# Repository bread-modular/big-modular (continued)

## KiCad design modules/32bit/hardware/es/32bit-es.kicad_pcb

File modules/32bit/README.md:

# 32bit — ESP32-S3 + CS4272 stereo audio processor (6HP)

S4 (2026-11-23): two boards. The **carrier** is the modules/usb-audio S5 analog board (CS4272 codec with
its own 24.576 MHz clock, NE5532 input / output stages, AMS1117 +5VA, DC-coupled ±5 V, 2 in / 2 out) with
two control pots, a MODE button and an LED in place of the volume pots. The **MCU board** (ESP32-S3R8,
8 MB PSRAM inside, W25Q128JVSIQ 16 MB flash, 40 MHz crystal) is soldered on two 1x10 strips over the
carrier's front side and carries the USB-C, which comes out through the front panel. Two M3x10 standoffs
above the MCU board take the plug forces. It runs the `master` end-of-chain processor in front of PA
systems; the reason for the codec change is in `docs/research.md` section 9. The S3 design (one board,
ES8388, MIDI and CV inputs, USB-C on the back) is in git history.

**ES1 variant (2026-11-23, `hardware/es/`, `docs/research.md` section 10):** the S3 board (ES8388, MIDI in,
2 audio + 2 CV in, back USB-C) with its own codec supply (LP5907 from +5V) and its own codec clock (11.2896 MHz
oscillator, ES8388 = I2S master), to build next to S4 and compare. Firmware: `BOARD=es1 ./compile.sh ...`.
Hand-routed, ERC 0 / DRC 0, JLCPCB export in [`jlcpcb/es/`](jlcpcb/es/README.md); not built.

| Panel (top to bottom) | Circuit |
|---|---|
| **USB** (USB-C) | MCU board J101 -> USBLC6-2SC6 -> ESP32-S3 GPIO19 / 20 (USB Serial/JTAG: Web Serial, console, firmware download). Data only, VBUS powers nothing |
| **IN L**, **IN R** | jack -> 1k -> NE5532 follower -> OPA1679 differential drive on +5VA -> CS4272 ADC (±5.5 V full scale, 100k input) |
| **P1**, **P2** | 50k RV09 from a filtered 3.03 V -> ESP32-S3 ADC1 (GPIO7 / GPIO6). Firmware controls, not in the audio path |
| LED, **MODE** | 3 mm red LED on GPIO39 (1k), 6 x 6 mm tact switch on GPIO38 (to GND) |
| **OUT L**, **OUT R** | CS4272 DAC (differential) -> NE5532 difference amplifier (±12 V) -> 1k -> jack (±5.3 V full scale) |

The ESP32-S3 is the I2S slave of the codec (SCLK GPIO18, LRCK GPIO17, data GPIO16 / GPIO13) and sets it
up over I2C (0x10, GPIO9 / GPIO8). Full pin map: [`docs/firmware-pins.md`](docs/firmware-pins.md).

Power: Eurorack 10-pin, ±12 V through series Schottkys; +12 V -> AMS1117-5.0 -> +5VA (codec analog side);
+12 V -> 22R 1 W -> AMS1117-3.3 -> +3V3 (MCU board, codec digital side behind a ferrite). About 130 mA
on +3V3 (datasheet estimate), so roughly 0.2 A from +12 V and 20 mA from -12 V; not measured. RESET and
BOOT buttons are on the carrier's back.

**Status: carrier S4 / R2 + MCU board S1 / R2, both hand-routed, 4 layers; panel P2. ERC 0, DRC 0,
0 unconnected, parity 0 on both boards. JLCPCB export in [`jlcpcb/`](jlcpcb/README.md) (two orders:
carrier 88 parts bottom side + panel, MCU board 25 parts top side, Economic PCBA). Fab-reviewed
2026-11-23; not supplier-accepted, not built.** The `master` firmware still needs its CS4272 driver.

| Path | Contents |
|---|---|
| `hardware/` | `32bit.kicad_{pro,sch,pcb}` (29 x 110 mm carrier) and `32bit-mcu.kicad_{pro,sch,pcb}` (29 x 29.55 mm MCU board), pinned symbols / footprints (`32BIT.kicad_sym`, `32BIT.pretty` + `PROVENANCE.json`, `32BIT.3dshapes`) |
| `panels/front-pcb/32bit-panel.kicad_{pro,pcb}` | 6HP FR4 front panel: NPTH only, USB-C slot, silkscreen labels |
| `panels/front-cad/` | FreeCAD printable panel (`.FCStd`, `.step`, `.stl`) generated from the panel PCB |
| `docs/research.md` | Decisions and circuit notes; section 9 is S4, 9.2 the fab review |
| `docs/geometry.json` | 6HP panel, placement and stack contract |
| `docs/32bit-schematic.pdf`, `docs/32bit-mcu-schematic.pdf`, `docs/fit/` | Schematic PDFs; native ERC / DRC JSON; assembly renders |
| `jlcpcb/` | JLCPCB Gerbers, BOM, CPL, upload map and sourcing notes |
| `firmware/` | `master`, `fxrack`, `polysynth` (ESP-IDF); see `firmware/README.md` |
| `tools/` | Generators (`circuit_carrier.py`, `circuit_mcu.py` hold the circuit tables), checks and the shared-tool profiles |

Checks (from `modules/32bit`):

```sh
python3 -B ../../opt/kicad-tools/kicad_tools.py check --config tools/kicad-project.json --reports research/check-NEW
python3 -B ../../opt/kicad-tools/kicad_tools.py check --config tools/kicad-project-mcu.json --reports research/check-mcu-NEW
python3 -B tools/check_edges.py     # courtyards to the edge, SMD to pot / jack pads
python3 -B tools/render_fit.py      # docs/fit/ renders of the stack
```

Both boards are routed by hand: `tools/build_layout.py` only rebuilds the panel now (`build_layout.py panel`).
Read [`Code.md`](Code.md) before changing hardware.

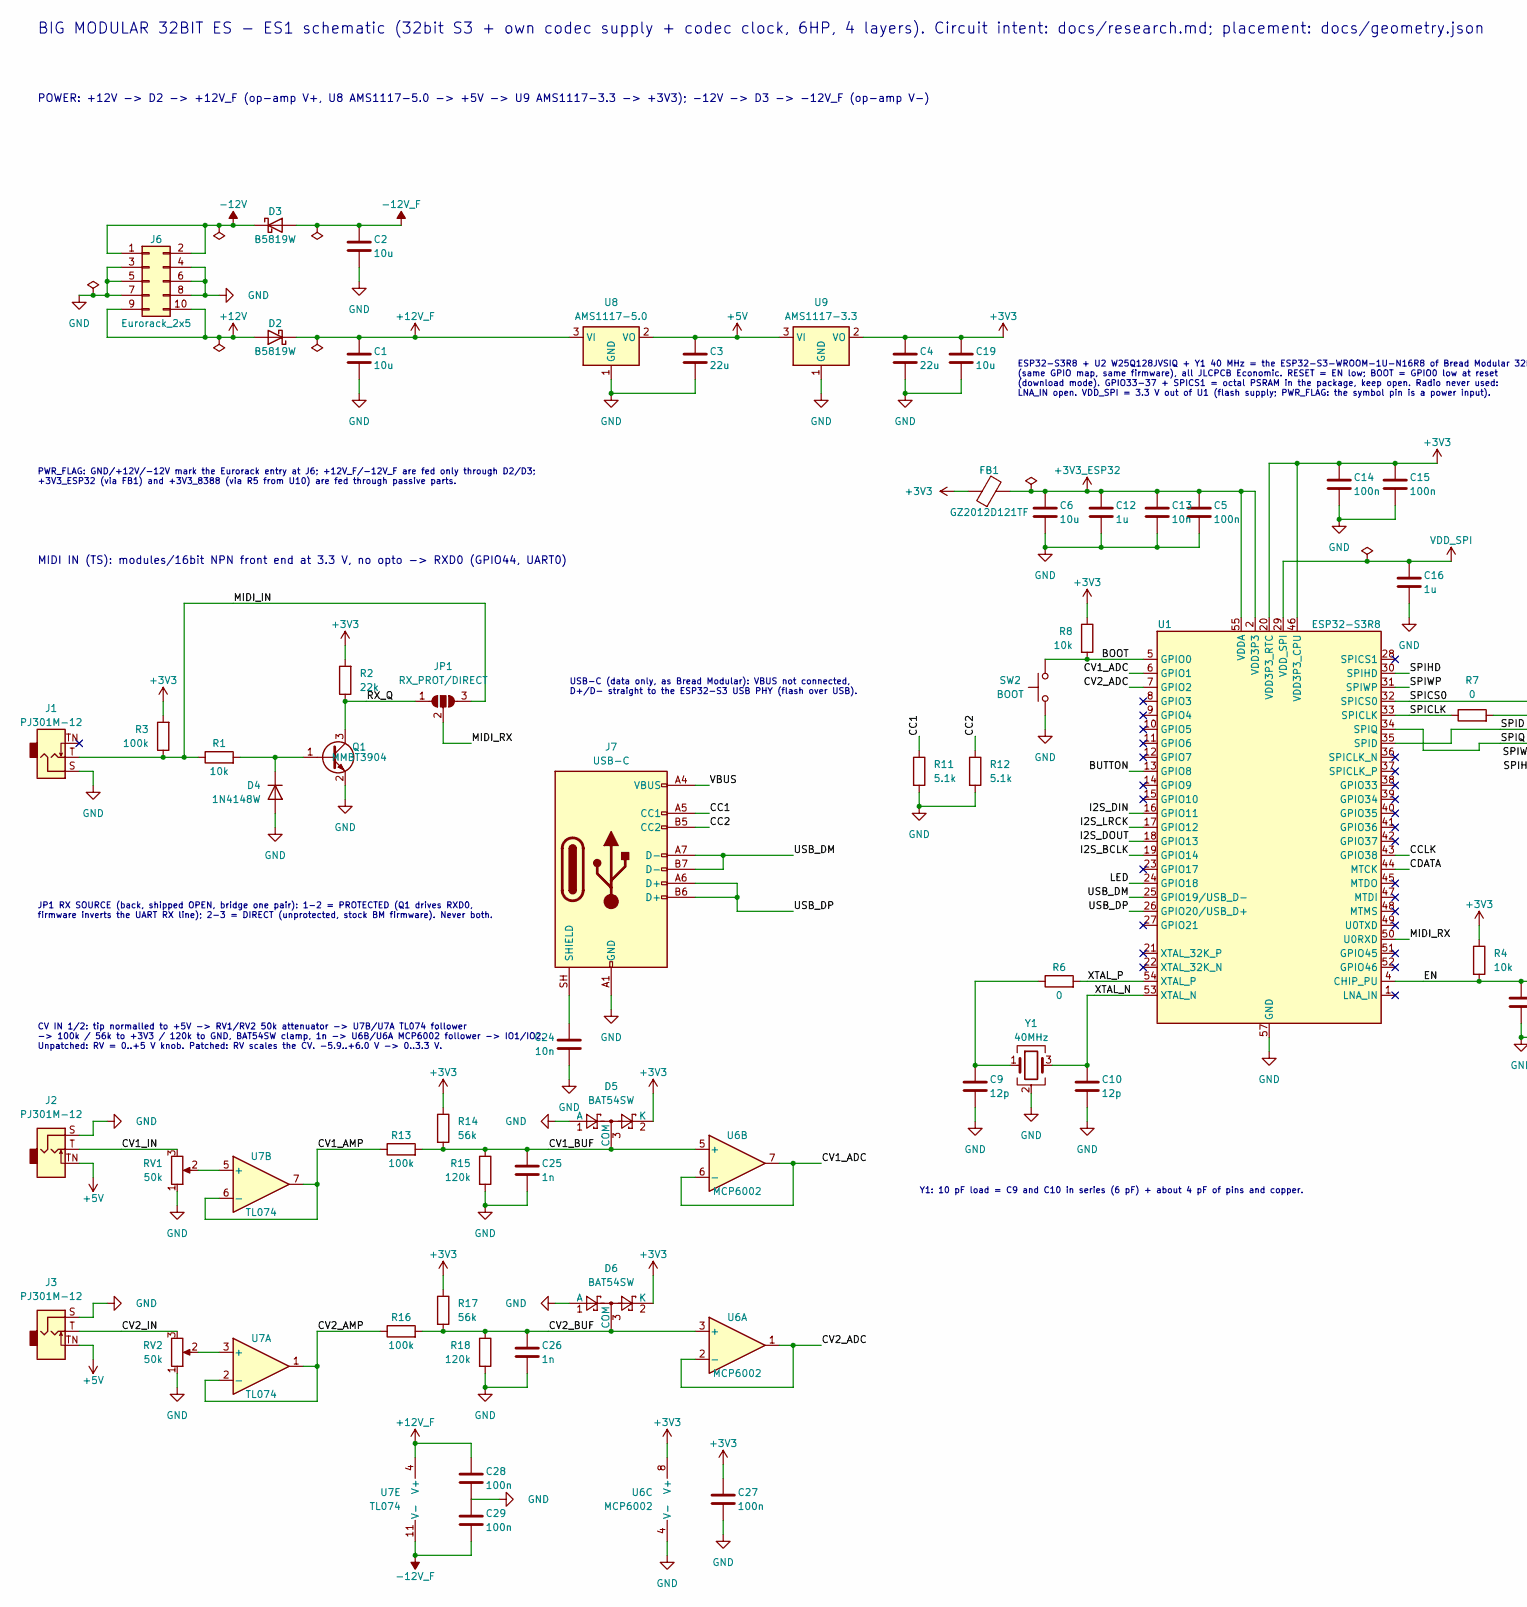
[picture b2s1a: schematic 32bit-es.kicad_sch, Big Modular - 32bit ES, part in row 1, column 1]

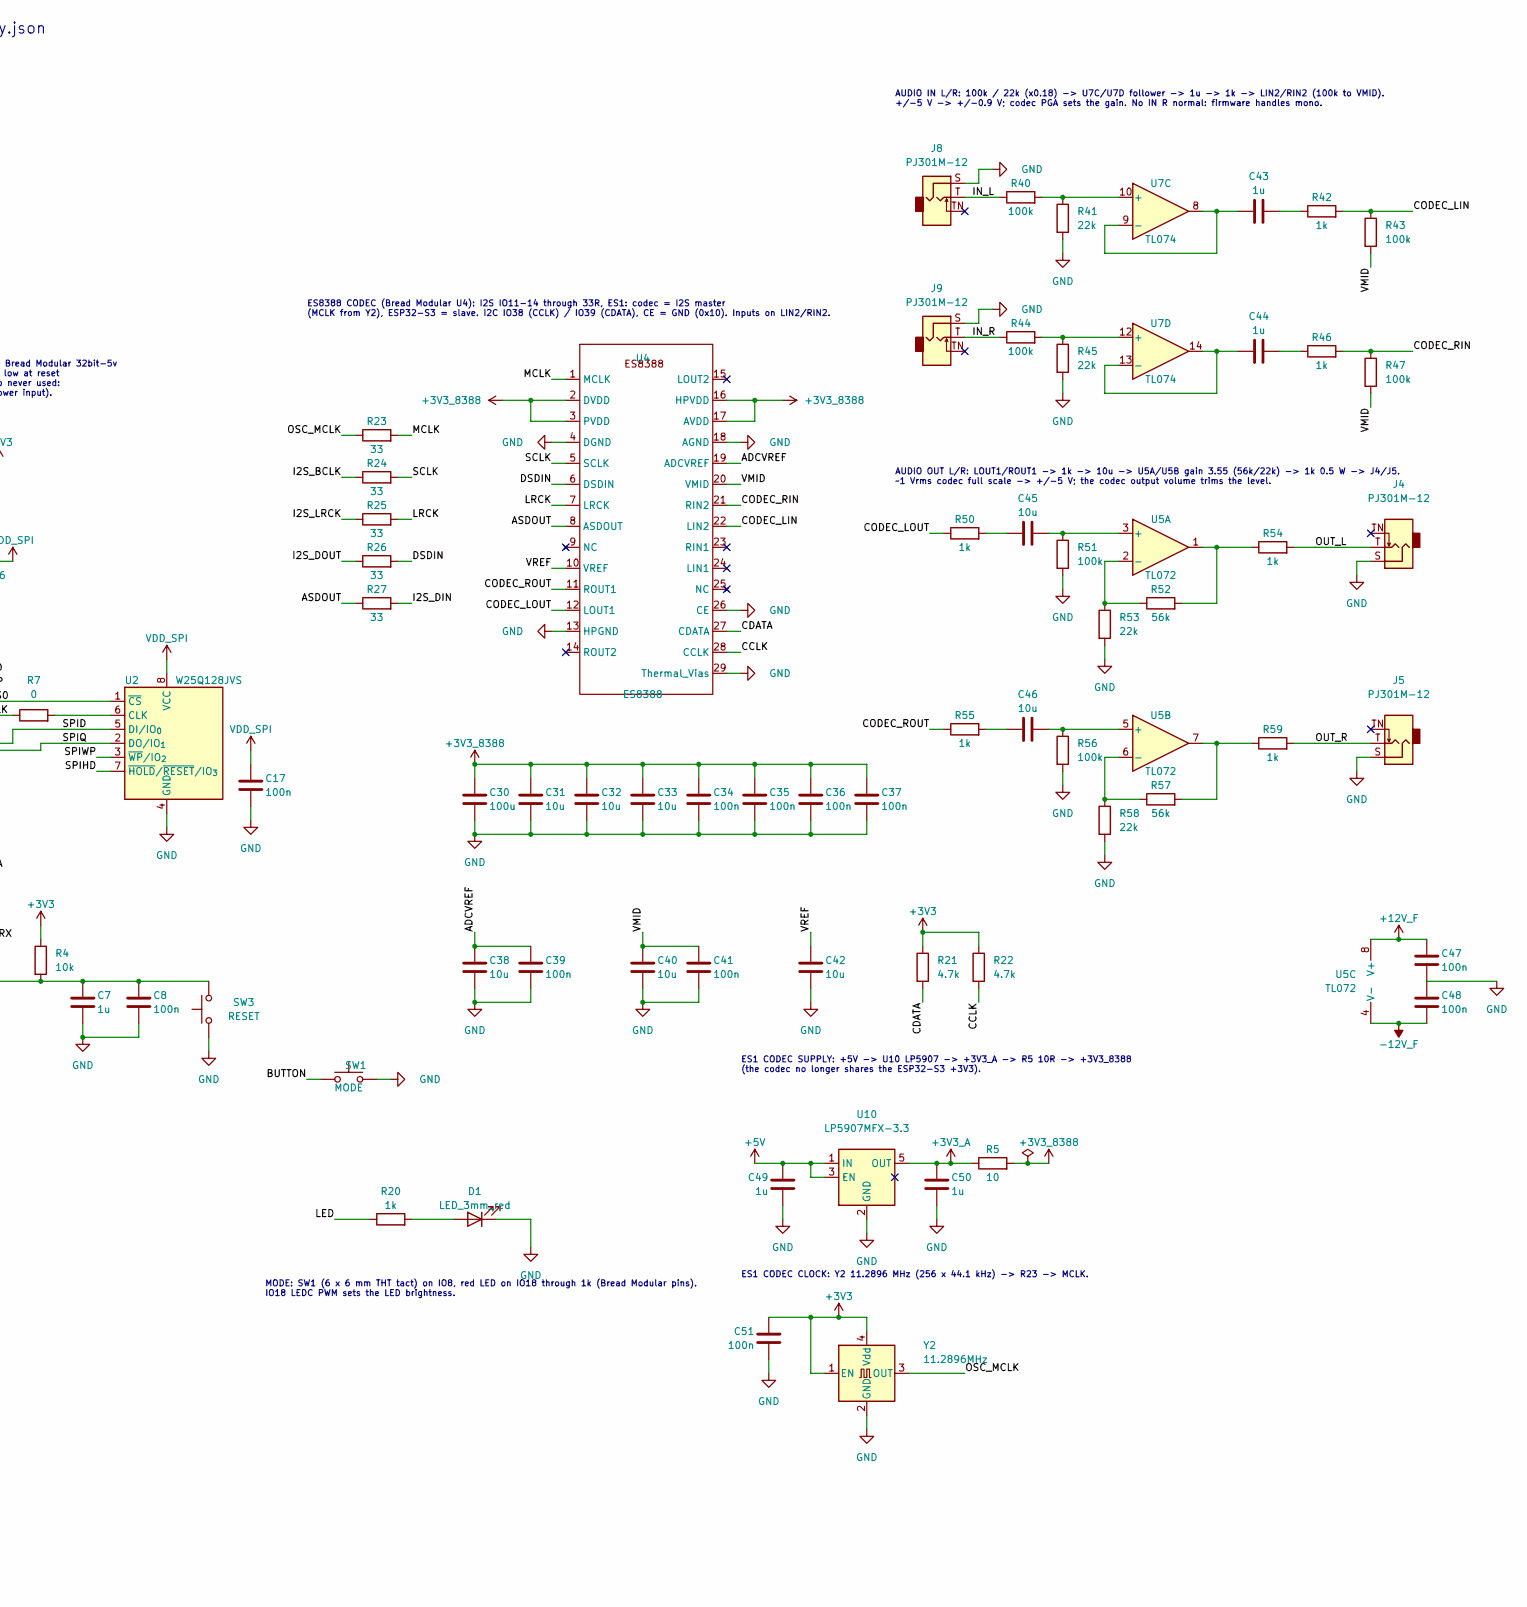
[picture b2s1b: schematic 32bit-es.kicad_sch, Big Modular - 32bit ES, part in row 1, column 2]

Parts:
C1, C2, C19, C45, C46: 10u; C_0805_2012Metric; Voltage 25V; MPN CL21A106KAYNNNE; LCSC C15850
C3, C4: 22u; C_0805_2012Metric; Voltage 25V; MPN CL21A226MAQNNNE; LCSC C45783
C5, C8, C14, C15, C17, C34, C35, C36, C37, C39, C41, C51: 100n; C_0402_1005Metric; Voltage 16V; MPN CL05B104KO5NNNC; LCSC C1525
C6: 10u; C_0603_1608Metric; Voltage 10V; MPN CL10A106KP8NNNC; LCSC C19702
C7, C12, C16, C43, C44, C49, C50: 1u; C_0402_1005Metric; Voltage 25V; MPN CL05A105KA5NQNC; LCSC C52923
C9, C10: 12p; C_0402_1005Metric; Voltage 50V; MPN 0402CG120J500NT; LCSC C1547
C13, C24: 10n; C_0402_1005Metric; Voltage 50V; MPN CL05B103KB5NNNC; LCSC C15195
C25, C26: 1n; C_0603_1608Metric; Voltage 50V; MPN CL10B102KB8NNNC; LCSC C1588
C27, C28, C29, C47, C48: 100n; C_0603_1608Metric; Voltage 50V; MPN CC0603KRX7R9BB104; LCSC C14663
C30: 100u; C_1206_3216Metric; Voltage 6.3V; MPN CL31A107MQHNNNE; LCSC C15008
C31, C32, C33, C38, C40, C42: 10u; C_0402_1005Metric; Voltage 10V; MPN CL05A106MQ5NUNC; LCSC C15525
D1: LED_3mm_red; LED_D3.0mm
D2, D3: B5819W; D_SOD-123; MPN B5819W SL; LCSC C8598
D4: 1N4148W; D_SOD-123; MPN 1N4148W; LCSC C81598
D5, D6: BAT54SW; SOT-323_SC-70; MPN BAT54SWT1G; LCSC C78260
FB1: GZ2012D121TF; C_0805_2012Metric; MPN GZ2012D121TF; LCSC C5671
J1, J2, J3, J4, J5, J8, J9: PJ301M-12; Jack_3.5mm_QingPu_WQP-PJ301M-12_Vertical
J6: Eurorack_2x5; PinHeader_2x05_P2.54mm_Vertical
J7: USB-C; USB_C_Receptacle_HRO_TYPE-C-31-M-12; MPN TYPE-C-31-M-12; LCSC C165948
JP1: RX_PROT/DIRECT; SolderJumper-3_P1.3mm_Open_RoundedPad1.0x1.5mm
Q1: MMBT3904; SOT-23; MPN MMBT3904(RANGE:100-300); LCSC C20526
R1: 10k; R_0603_1608Metric; MPN 0603WAF1002T5E; LCSC C25804
R2, R41, R45, R53, R58: 22k; R_0603_1608Metric; MPN 0603WAF2202T5E; LCSC C31850
R3, R13, R16, R40, R44, R51, R56: 100k; R_0603_1608Metric; MPN 0603WAF1003T5E; LCSC C25803
R4, R8: 10k; R_0402_1005Metric; MPN 0402WGF1002TCE; LCSC C25744
R5: 10; R_0603_1608Metric; MPN 0603WAF100JT5E; LCSC C22859
R6: 0; R_0402_1005Metric; MPN 0402WGF0000TCE; LCSC C17168
R7: 0; R_0603_1608Metric; MPN 0603WAF0000T5E; LCSC C21189
R11, R12: 5.1k; R_0402_1005Metric; MPN 0402WGF5101TCE; LCSC C25905
R14, R17, R52, R57: 56k; R_0603_1608Metric; MPN 0603WAF5602T5E; LCSC C23206
R15, R18: 120k; R_0603_1608Metric; MPN 0603WAF1203T5E; LCSC C25808
R20, R42, R46, R50, R55: 1k; R_0603_1608Metric; MPN 0603WAF1001T5E; LCSC C21190
R21, R22: 4.7k; R_0402_1005Metric; MPN 0402WGF4701TCE; LCSC C25900
R23, R24, R25, R26, R27: 33; R_0402_1005Metric; MPN 0402WGF330JTCE; LCSC C25105
R43, R47: 100k; R_0402_1005Metric; MPN 0402WGF1003TCE; LCSC C25741
R54, R59: 1k; R_1206_3216Metric; MPN 1206W4F1001T5E; LCSC C4410
RV1, RV2: 50k; Potentiometer_RV09
SW1: MODE; SW_PUSH_6mm_H7.3mm; MPN 6x6x7 mm THT tact switch, 4 pins (gener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
SW2: BOOT; K2-1808SN-A4SW-01; MPN K2-1808SN-A4SW-01; LCSC C92589
SW3: RESET; K2-1808SN-A4SW-01; MPN K2-1808SN-A4SW-01; LCSC C92589
U1: ESP32-S3R8; QFN-56-1EP_7x7mm_P0.4mm_EP4x4mm_ThermalVias; MPN ESP32-S3R8; LCSC C2913194
U2: W25Q128JVS; SOIC-8_5.3x5.3mm_P1.27mm; MPN W25Q128JVSIQ; LCSC C97521
U4: ES8388; ES8388_QFN28_4x4_P0.45_EP2.6_ThermalVias; MPN ES8388; LCSC C365736
U5: TL072; SOIC-8_3.9x4.9mm_P1.27mm; MPN TL072CDT; LCSC C6961
U6: MCP6002; SOIC-8_3.9x4.9mm_P1.27mm; MPN MCP6002T-I/SN; LCSC C7377
U7: TL074; SOIC-14_3.9x8.7mm_P1.27mm; MPN TL074CDR; LCSC C12594
U8: AMS1117-5.0; SOT-223-3_TabPin2; MPN AMS1117-5.0; LCSC C6187
U9: AMS1117-3.3; SOT-223-3_TabPin2; MPN AMS1117-3.3; LCSC C6186
U10: LP5907MFX-3.3; SOT-23-5; MPN LP5907MFX-3.3/NOPB; LCSC C80670
Y1: 40MHz; Crystal_SMD_3225-4Pin_3.2x2.5mm; MPN X322540MMB4SI; LCSC C5210647
Y2: 11.2896MHz; Oscillator_SMD_Abracon_ASE-4Pin_3.2x2.5mm; MPN OT322511.2896MJBA4SL; LCSC C2831381

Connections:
+3V3: C4.1, C14.1, C15.1, C19.1, C27.1, C51.1, D5.2 (K), D6.2 (K), FB1.1, R2.2, R3.2, R4.1, R8.1, R14.1, R17.1, R21.1, R22.1, U1.20 (VDD3P3_RTC), U1.46 (VDD3P3_CPU), U6.8 (V+), U9.2 (VO), Y2.1 (EN), Y2.4 (Vdd)
+3V3_8388: C30.1, C31.1, C32.1, C33.1, C34.1, C35.1, C36.1, C37.1, R5.2, U4.2 (DVDD), U4.3 (PVDD), U4.16 (HPVDD), U4.17 (AVDD)
+3V3_A: C50.1, R5.1, U10.5 (OUT)
+3V3_ESP32: C5.1, C6.1, C12.1, C13.1, FB1.2, U1.2 (VDD3P3), U1.3 (VDD3P3), U1.55 (VDDA), U1.56 (VDDA)
+5V: C3.1, C49.1, J2.TN, J3.TN, U8.2 (VO), U9.3 (VI), U10.1 (IN), U10.3 (EN)
+12V: D2.2 (A), J6.9, J6.10
+12V_F: C1.1, C28.1, C47.1, D2.1 (K), U5.8 (V+), U7.4 (V+), U8.3 (VI)
-12V: D3.1 (K), J6.1, J6.2
-12V_F: C2.2, C29.2, C48.2, D3.2 (A), U5.4 (V-), U7.11 (V-)
/ADCVREF: C38.1, C39.1, U4.19 (ADCVREF)
/ASDOUT: R27.1, U4.8 (ASDOUT)
/BOOT: R8.2, SW2.2, U1.5 (GPIO0)
/BUTTON: SW1.1, U1.13 (GPIO8)
/CC1: J7.A5 (CC1), R11.1
/CC2: J7.B5 (CC2), R12.1
/CCLK: R22.2, U1.43 (GPIO38), U4.28 (CCLK)
/CDATA: R21.2, U1.44 (MTCK), U4.27 (CDATA)
/CODEC_LIN: R42.2, R43.1, U4.22 (LIN2)
/CODEC_LOUT: R50.1, U4.12 (LOUT1)
/CODEC_RIN: R46.2, R47.1, U4.21 (RIN2)
/CODEC_ROUT: R55.1, U4.11 (ROUT1)
/CV1_ADC: U1.6 (GPIO1), U6.6 (-), U6.7
/CV1_AMP: R13.1, U7.6 (-), U7.7
/CV1_BUF: C25.1, D5.3 (COM), R13.2, R14.2, R15.1, U6.5 (+)
/CV1_IN: J2.T, RV1.3
/CV2_ADC: U1.7 (GPIO2), U6.1, U6.2 (-)
/CV2_AMP: R16.1, U7.1, U7.2 (-)
/CV2_BUF: C26.1, D6.3 (COM), R16.2, R17.2, R18.1, U6.3 (+)
/CV2_IN: J3.T, RV2.3
/DSDIN: R26.2, U4.6 (DSDIN)
/EN: C7.1, C8.1, R4.2, SW3.2, U1.4 (CHIP_PU)
/I2S_BCLK: R24.1, U1.19 (GPIO14)
/I2S_DIN: R27.2, U1.16 (GPIO11)
/I2S_DOUT: R26.1, U1.18 (GPIO13)
/I2S_LRCK: R25.1, U1.17 (GPIO12)
/IN_L: J8.T, R40.1
/IN_R: J9.T, R44.1
/LED: R20.1, U1.24 (GPIO18)
/LRCK: R25.2, U4.7 (LRCK)
/MCLK: R23.2, U4.1 (MCLK)
/MIDI_IN: J1.T, JP1.3 (B), R1.1, R3.1
/MIDI_RX: JP1.2 (C), U1.50 (U0RXD)
/OSC_MCLK: R23.1, Y2.3 (OUT)
/OUT_L: J4.T, R54.2
/OUT_R: J5.T, R59.2
/RX_Q: JP1.1 (A), Q1.3 (C), R2.1
/SCLK: R24.2, U4.5 (SCLK)
/SPICLK: R7.1, U1.33 (SPICLK)
/SPICS0: U1.32 (SPICS0), U2.1 (~CS)
/SPID: U1.35 (SPID), U2.5 (DI/IO_{0})
/SPIHD: U1.30 (SPIHD), U2.7 (~HOLD/~RESET/IO_{3})
/SPIQ: U1.34 (SPIQ), U2.2 (DO/IO_{1})
/SPIWP: U1.31 (SPIWP), U2.3 (~WP/IO_{2})
/USB_DM: J7.A7 (D-), J7.B7 (D-), U1.25 (GPIO19/USB_D-)
/USB_DP: J7.A6 (D+), J7.B6 (D+), U1.26 (GPIO20/USB_D+)
/VBUS: J7.A4 (VBUS), J7.A9 (VBUS), J7.B4 (VBUS), J7.B9 (VBUS)
/VMID: C40.1, C41.1, R43.2, R47.2, U4.20 (VMID)
/VREF: C42.1, U4.10 (VREF)
/XTAL_N: C10.1, U1.53 (XTAL_N), Y1.3
/XTAL_P: R6.2, U1.54 (XTAL_P)
GND: C1.2, C2.1, C3.2, C4.2, C5.2, C6.2, C7.2, C8.2, C9.2, C10.2, C12.2, C13.2, C14.2, C15.2, C16.2, C17.2, C19.2, C24.2, C25.2, C26.2, C27.2, C28.2, C29.1, C30.2, C31.2, C32.2, C33.2, C34.2, C35.2, C36.2, C37.2, C38.2, C39.2, C40.2, C41.2, C42.2, C47.2, C48.1, C49.2, C50.2, C51.2, D1.1 (K), D4.2 (A), D5.1 (A), D6.1 (A), J1.S, J2.S, J3.S, J4.S, J5.S, J6.3, J6.4, J6.5, J6.6, J6.7, J6.8, J7.A1 (GND), J7.A12 (GND), J7.B1 (GND), J7.B12 (GND), J8.S, J9.S, Q1.2 (E), R11.2, R12.2, R15.2, R18.2, R41.2, R45.2, R51.2, R53.2, R56.2, R58.2, RV1.1, RV2.1, SW1.2, SW2.1, SW3.1, U1.57 (GND), U2.4 (GND), U4.4 (DGND), U4.13 (HPGND), U4.18 (AGND), U4.26 (CE), U4.29 (Thermal_Vias), U6.4 (V-), U8.1 (GND), U9.1 (GND), U10.2 (GND), Y1.2 (G), Y1.4 (G), Y2.2 (GND)
unnamed: C9.1, R6.1, Y1.1
unnamed: C43.2, R42.1
unnamed: C44.2, R46.1
unnamed: C45.1, R50.2
unnamed: C46.1, R55.2
unnamed: D1.2 (A), R20.2
unnamed: D4.1 (K), Q1.1 (B), R1.2
unnamed: C24.1, J7.SH (SHIELD)
unnamed: R52.2, R54.1, U5.1
unnamed: R57.2, R59.1, U5.7
unnamed: R7.2, U2.6 (CLK)
unnamed: C45.2, R51.1, U5.3 (+)
unnamed: R52.1, R53.1, U5.2 (-)
unnamed: C46.2, R56.1, U5.5 (+)
unnamed: R57.1, R58.1, U5.6 (-)
unnamed: RV2.2, U7.3 (+)
unnamed: RV1.2, U7.5 (+)
unnamed: R40.2, R41.1, U7.10 (+)
unnamed: C43.1, U7.8, U7.9 (-)
unnamed: R44.2, R45.1, U7.12 (+)
unnamed: C44.1, U7.13 (-), U7.14
VDD_SPI: C16.1, C17.1, U1.29 (VDD_SPI), U2.8 (VCC)

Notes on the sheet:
USB-C (data only, as Bread Modular): VBUS not connected, D+/D- straight to the ESP32-S3 USB PHY (flash over USB).
MIDI IN (TS): modules/16bit NPN front end at 3.3 V, no opto -> RXD0 (GPIO44, UART0)
ES8388 CODEC (Bread Modular U4): I2S IO11-14 through 33R, ES1: codec = I2S master (MCLK from Y2), ESP32-S3 = slave. I2C IO38 (CCLK) / IO39 (CDATA), CE = GND (0x10). Inputs on LIN2/RIN2.
POWER: +12V -> D2 -> +12V_F (op-amp V+, U8 AMS1117-5.0 -> +5V -> U9 AMS1117-3.3 -> +3V3); -12V -> D3 -> -12V_F (op-amp V-)
JP1 RX SOURCE (back, shipped OPEN, bridge one pair): 1-2 = PROTECTED (Q1 drives RXD0, firmware inverts the UART RX line); 2-3 = DIRECT (unprotected, stock BM firmware). Never both.
ES1 CODEC SUPPLY: +5V -> U10 LP5907 -> +3V3_A -> R5 10R -> +3V3_8388 (the codec no longer shares the ESP32-S3 +3V3).
ES1 CODEC CLOCK: Y2 11.2896 MHz (256 x 44.1 kHz) -> R23 -> MCLK.
BIG MODULAR 32BIT ES - ES1 schematic (32bit S3 + own codec supply + codec clock, 6HP, 4 layers). Circuit intent: docs/research.md; placement: docs/geometry.json
AUDIO IN L/R: 100k / 22k (x0.18) -> U7C/U7D follower -> 1u -> 1k -> LIN2/RIN2 (100k to VMID). +/-5 V -> +/-0.9 V; codec PGA sets the gain. No IN R normal: firmware handles mono.
ESP32-S3R8 + U2 W25Q128JVSIQ + Y1 40 MHz = the ESP32-S3-WROOM-1U-N16R8 of Bread Modular 32bit-5v (same GPIO map, same firmware), all JLCPCB Economic. RESET = EN low; BOOT = GPIO0 low at reset (download mode). GPIO33-37 + SPICS1 = octal PSRAM in the package, keep open. Radio never used: LNA_IN open.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
CV IN 1/2: tip normalled to +5V -> RV1/RV2 50k attenuator -> U7B/U7A TL074 follower -> 100k / 56k to +3V3 / 120k to GND, BAT54SW clamp, 1n -> U6B/U6A MCP6002 follower -> IO1/IO2. Unpatched: RV = 0..+5 V knob. Patched: RV scales the CV. -5.9..+6.0 V -> 0..3.3 V.
PWR_FLAG: GND/+12V/-12V mark the Eurorack entry at J6; +12V_F/-12V_F are fed only through D2/D3; +3V3_ESP32 (via FB1) and +3V3_8388 (via R5 from U10) are fed through passive parts.
MODE: SW1 (6 x 6 mm THT tact) on IO8, red LED on IO18 through 1k (Bread Modular pins). IO18 LEDC PWM sets the LED brightness.
AUDIO OUT L/R: LOUT1/ROUT1 -> 1k -> 10u -> U5A/U5B gain 3.55 (56k/22k) -> 1k 0.5 W -> J4/J5. ~1 Vrms codec full scale -> +/-5 V; the codec output volume trims the level.
Y1: 10 pF load = C9 and C10 in series (6 pF) + about 4 pF of pins and copper.

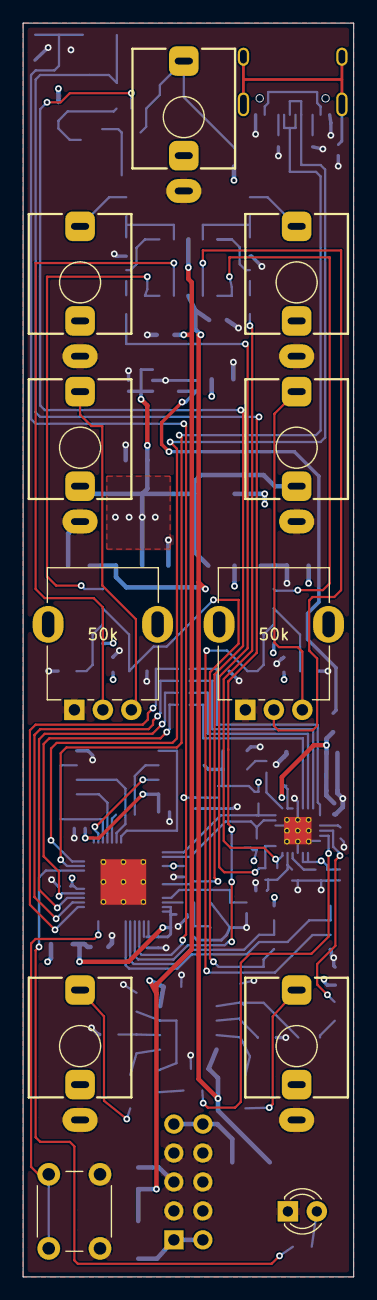
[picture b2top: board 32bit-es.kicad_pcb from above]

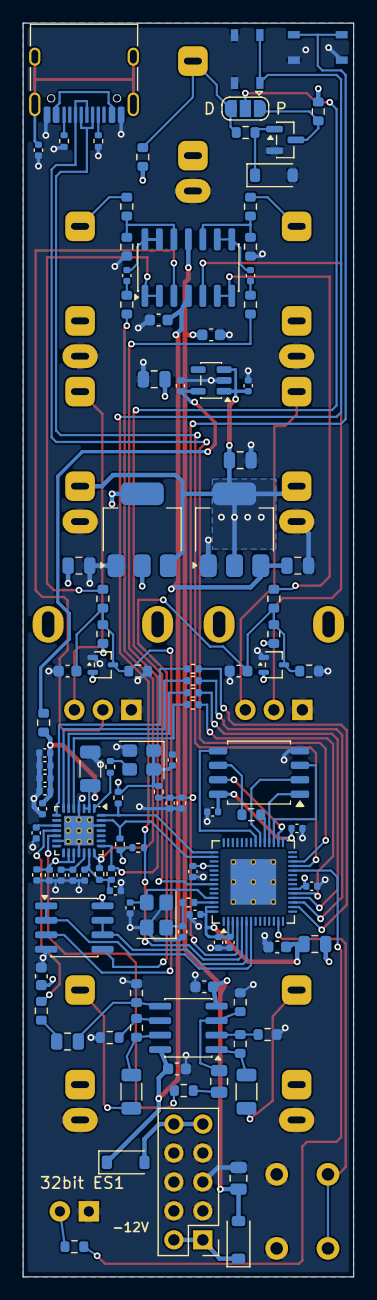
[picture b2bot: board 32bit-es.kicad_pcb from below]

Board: 4 copper layers, 29.0 x 110.0 mm, 121 parts (110 on the bottom side), 83 nets.

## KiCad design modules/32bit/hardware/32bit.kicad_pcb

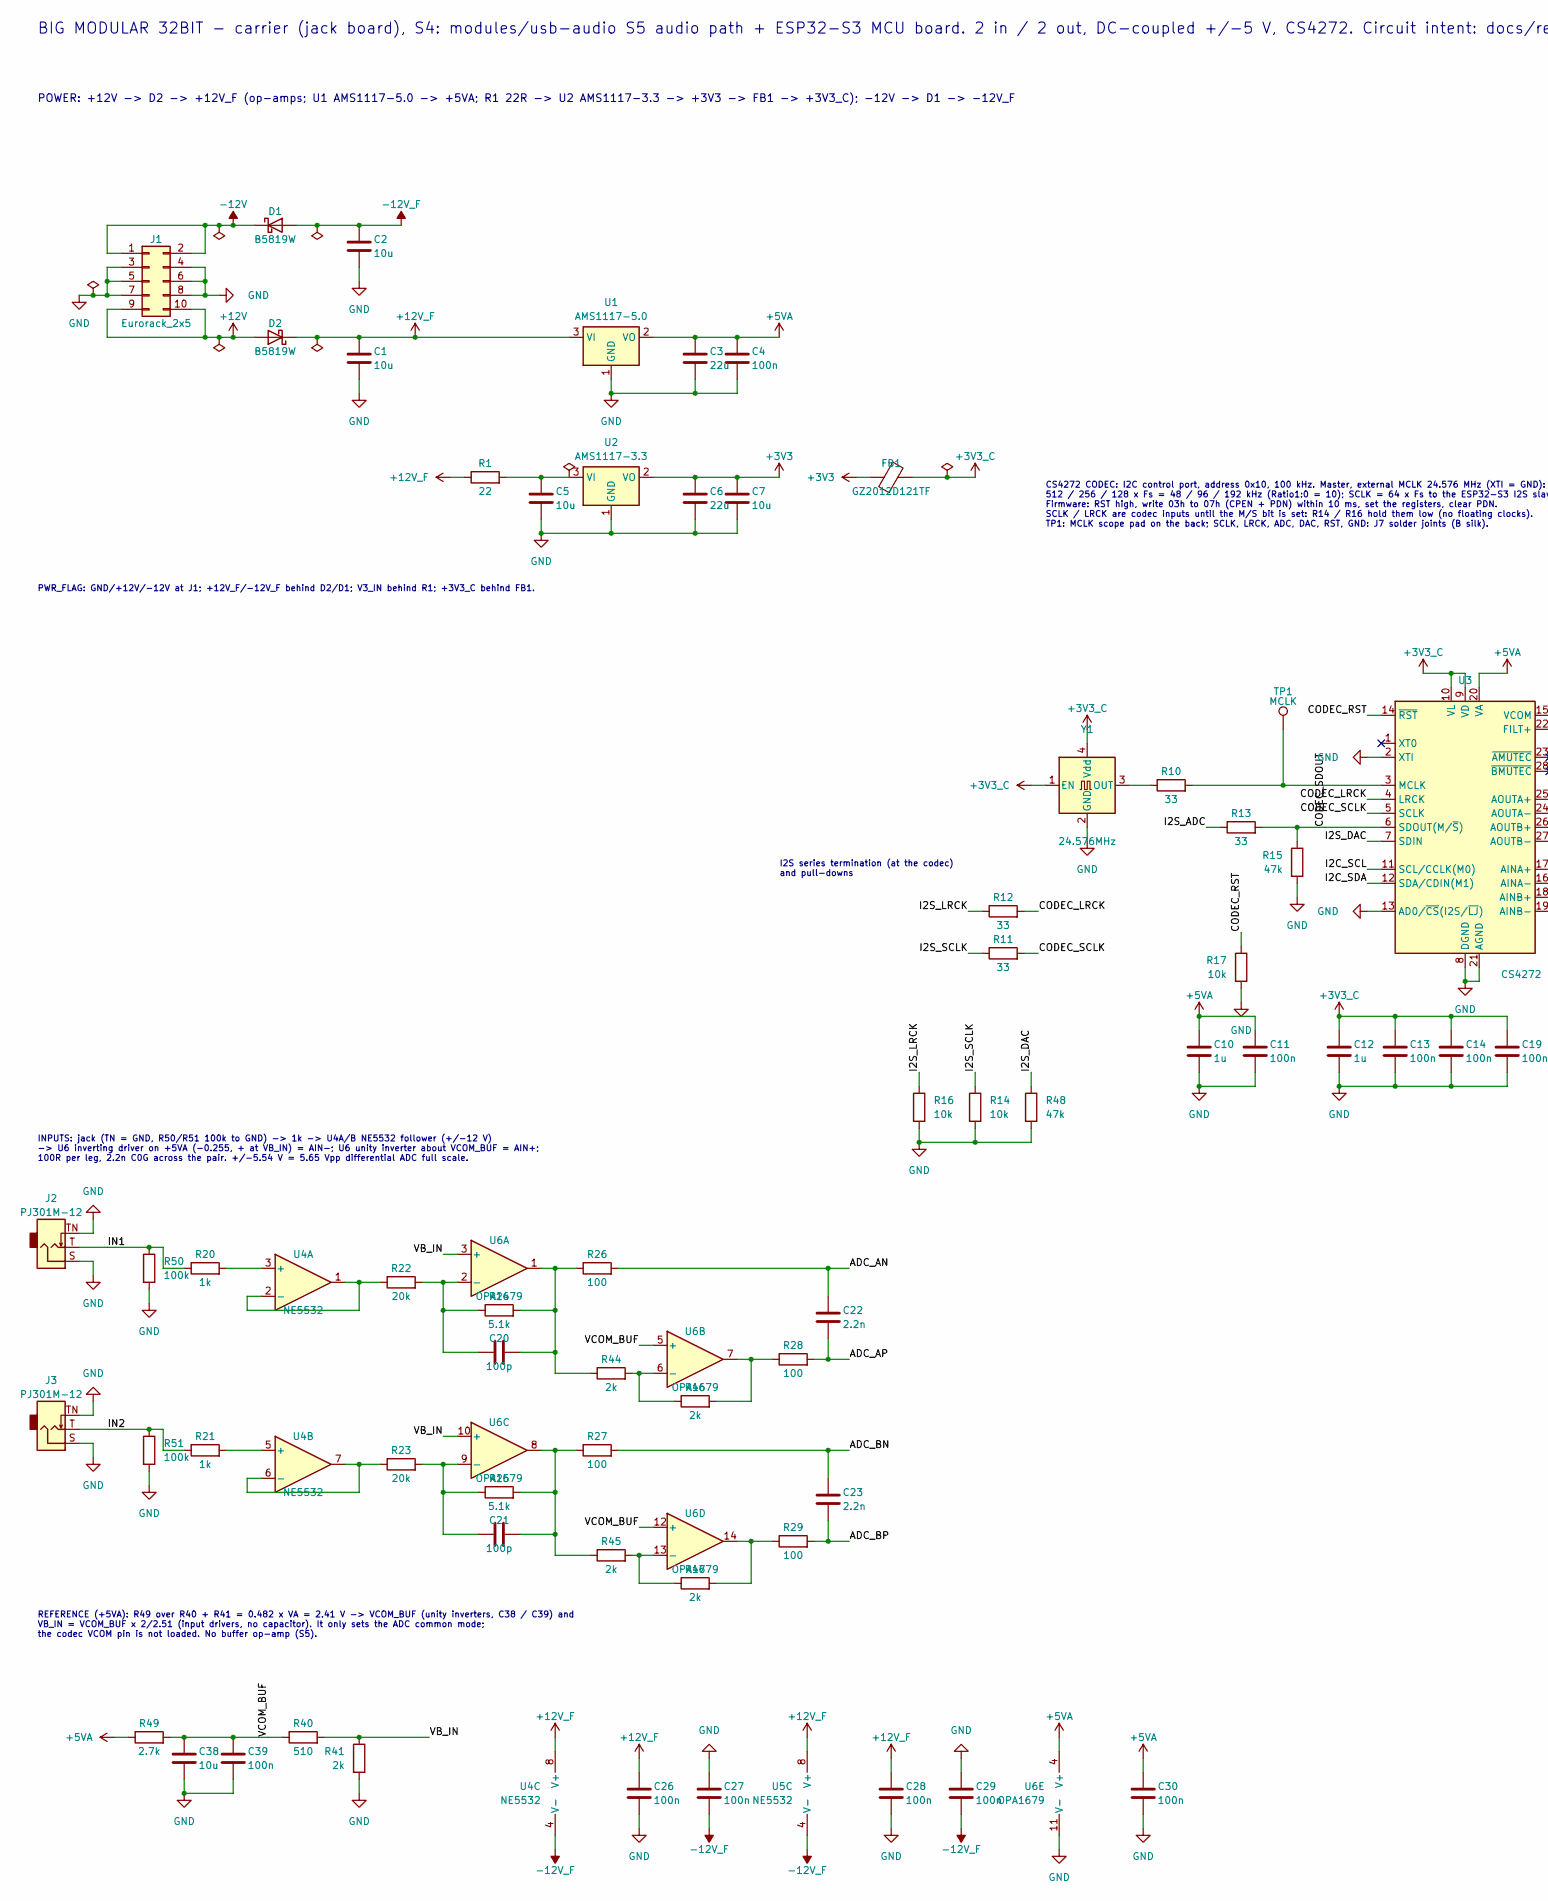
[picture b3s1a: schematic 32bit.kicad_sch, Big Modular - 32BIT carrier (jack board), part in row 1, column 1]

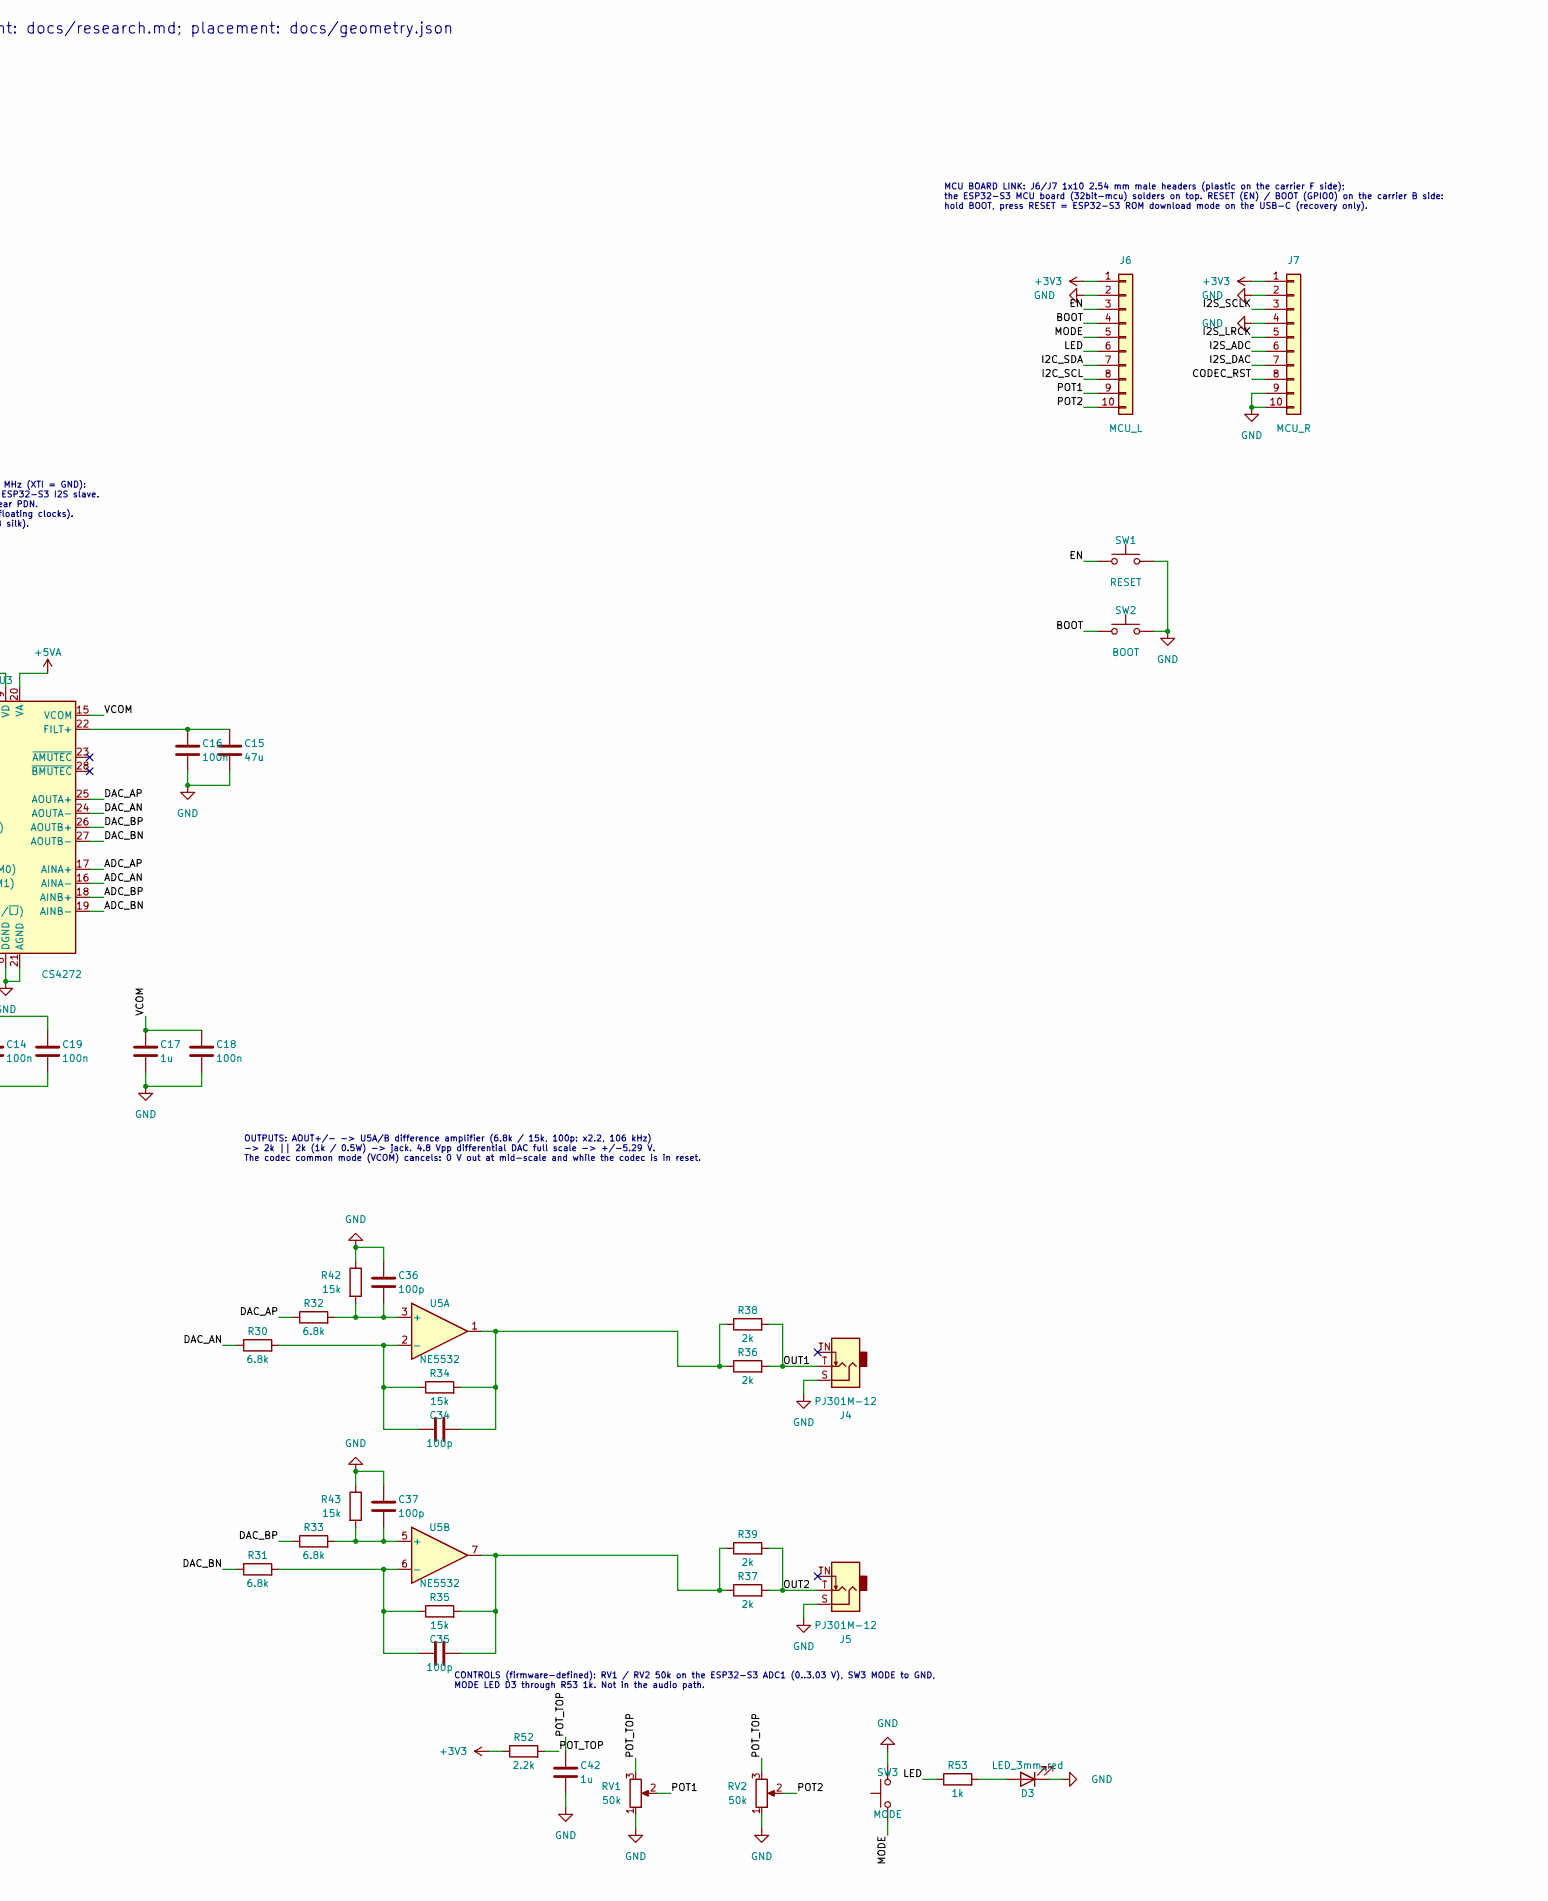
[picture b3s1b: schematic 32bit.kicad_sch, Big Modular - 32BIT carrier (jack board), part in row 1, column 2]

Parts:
C1, C2, C5, C7, C38: 10u; C_0805_2012Metric; Voltage 25V; MPN CL21A106KAYNNNE; LCSC C15850
C3, C6: 22u; C_0805_2012Metric; Voltage 25V; MPN CL21A226MAQNNNE; LCSC C45783
C4, C11, C13, C14, C16, C18, C19, C26, C27, C28, C29, C30, C39: 100n; C_0603_1608Metric; Voltage 50V; MPN CC0603KRX7R9BB104; LCSC C14663
C10, C12, C17, C42: 1u; C_0603_1608Metric; Voltage 50V; MPN CL10A105KB8NNNC; LCSC C15849
C15: 47u; C_0805_2012Metric; Voltage 6.3V; MPN CL21A476MQYNNNE; LCSC C16780
C20, C21, C34, C35, C36, C37: 100p; C_0603_1608Metric; Voltage 50V; MPN CL10C101JB8NNNC; LCSC C14858
C22, C23: 2.2n; C_0603_1608Metric; Voltage 50V; MPN CC0603JRNPO9BN222; LCSC C107043
D1, D2: B5819W; D_SOD-123; MPN B5819W SL; LCSC C8598
D3: LED_3mm_red; LED_D3.0mm
FB1: GZ2012D121TF; C_0805_2012Metric; MPN GZ2012D121TF; LCSC C5671
J1: Eurorack_2x5; PinHeader_2x05_P2.54mm_Vertical
J2, J3, J4, J5: PJ301M-12; Jack_3.5mm_QingPu_WQP-PJ301M-12_Vertical
J6: MCU_L; PinHeader_1x10_P2.54mm_Vertical; MPN 2.54 mm 1x10 male pin header (2.5 mm pl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
J7: MCU_R; PinHeader_1x10_P2.54mm_Vertical; MPN 2.54 mm 1x10 male pin header (2.5 mm pl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
R1: 22; R_2512_6332Metric; MPN 25121WF220JT4E; LCSC C118189
R10, R11, R12, R13: 33; R_0603_1608Metric; MPN 0603WAF330JT5E; LCSC C23140
R14, R16, R17: 10k; R_0603_1608Metric; MPN 0603WAF1002T5E; LCSC C25804
R15, R48: 47k; R_0603_1608Metric; MPN 0603WAF4702T5E; LCSC C25819
R20, R21, R53: 1k; R_0603_1608Metric; MPN 0603WAF1001T5E; LCSC C21190
R22, R23: 20k; R_0603_1608Metric; MPN 0603WAF2002T5E; LCSC C4184
R24, R25: 5.1k; R_0603_1608Metric; MPN 0603WAF5101T5E; LCSC C23186
R26, R27, R28, R29: 100; R_0603_1608Metric; MPN 0603WAF1000T5E; LCSC C22775
R30, R31, R32, R33: 6.8k; R_0603_1608Metric; MPN 0603WAF6801T5E; LCSC C23212
R34, R35, R42, R43: 15k; R_0603_1608Metric; MPN 0603WAF1502T5E; LCSC C22809
R36, R37, R38, R39: 2k; R_1206_3216Metric; Tolerance 1%; MPN 1206W4F2001T5E; LCSC C17944
R40: 510; R_0603_1608Metric; MPN 0603WAF5100T5E; LCSC C23193
R41, R44, R45, R46, R47: 2k; R_0603_1608Metric; MPN 0603WAF2001T5E; LCSC C22975
R49: 2.7k; R_0603_1608Metric; MPN 0603WAF2701T5E; LCSC C13167
R50, R51: 100k; R_0603_1608Metric; MPN 0603WAF1003T5E; LCSC C25803
R52: 2.2k; R_0603_1608Metric; MPN 0603WAF2201T5E; LCSC C4190
RV1, RV2: 50k; Potentiometer_RV09
SW1: RESET; K2-1808SN-A4SW-01; MPN K2-1808SN-A4SW-01; LCSC C92589
SW2: BOOT; K2-1808SN-A4SW-01; MPN K2-1808SN-A4SW-01; LCSC C92589
SW3: MODE; SW_PUSH_6mm_H7.3mm
TP1: MCLK; TestPoint_Pad_D1.5mm
U1: AMS1117-5.0; SOT-223-3_TabPin2; MPN AMS1117-5.0; LCSC C6187
U2: AMS1117-3.3; SOT-223-3_TabPin2; MPN AMS1117-3.3; LCSC C6186
U3: CS4272; TSSOP-28_4.4x9.7mm_P0.65mm; MPN CS4272-CZZR; LCSC C2151111
U4, U5: NE5532; SOIC-8_3.9x4.9mm_P1.27mm; MPN NE5532DR; LCSC C7426
U6: OPA1679; SOIC-14_3.9x8.7mm_P1.27mm; MPN OPA1679IDR; LCSC C2878631
Y1: 24.576MHz; Oscillator_SMD_Abracon_ASE-4Pin_3.2x2.5mm; MPN OT2EL4C4JI-111OLP-24.576M; LCSC C5203547

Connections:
+3V3: C6.1, C7.1, FB1.1, J6.1, J7.1, R52.1, U2.2 (VO)
+3V3_C: C12.1, C13.1, C14.1, C19.1, FB1.2, U3.9 (VD), U3.10 (VL), Y1.1 (EN), Y1.4 (Vdd)
+5VA: C3.1, C4.1, C10.1, C11.1, C30.1, R49.1, U1.2 (VO), U3.20 (VA), U6.4 (V+)
+12V: D2.2 (A), J1.9, J1.10
+12V_F: C1.1, C26.1, C28.1, D2.1 (K), R1.1, U1.3 (VI), U4.8 (V+), U5.8 (V+)
-12V: D1.1 (K), J1.1, J1.2
-12V_F: C2.2, C27.2, C29.2, D1.2 (A), U4.4 (V-), U5.4 (V-)
/ADC_AN: C22.1, R26.2, U3.16 (AINA-)
/ADC_AP: C22.2, R28.2, U3.17 (AINA+)
/ADC_BN: C23.1, R27.2, U3.19 (AINB-)
/ADC_BP: C23.2, R29.2, U3.18 (AINB+)
/BOOT: J6.4, SW2.1
/CODEC_LRCK: R12.2, U3.4 (LRCK)
/CODEC_RST: J7.8, R17.1, U3.14 (~RST)
/CODEC_SCLK: R11.2, U3.5 (SCLK)
/CODEC_SDOUT: R13.2, R15.1, U3.6 (SDOUT(M/~S))
/DAC_AN: R30.1, U3.24 (AOUTA-)
/DAC_AP: R32.1, U3.25 (AOUTA+)
/DAC_BN: R31.1, U3.27 (AOUTB-)
/DAC_BP: R33.1, U3.26 (AOUTB+)
/EN: J6.3, SW1.1
/I2C_SCL: J6.8, U3.11 (SCL/CCLK(M0))
/I2C_SDA: J6.7, U3.12 (SDA/CDIN(M1))
/I2S_ADC: J7.6, R13.1
/I2S_DAC: J7.7, R48.1, U3.7 (SDIN)
/I2S_LRCK: J7.5, R12.1, R16.1
/I2S_SCLK: J7.3, R11.1, R14.1
/IN1: J2.T, R20.1, R50.1
/IN2: J3.T, R21.1, R51.1
/LED: J6.6, R53.1
/MODE: J6.5, SW3.1
/OUT1: J4.T, R36.2, R38.2
/OUT2: J5.T, R37.2, R39.2
/POT1: J6.9, RV1.2
/POT2: J6.10, RV2.2
/POT_TOP: C42.1, R52.2, RV1.3, RV2.3
/VB_IN: R40.2, R41.1, U6.3 (+), U6.10 (+)
/VCOM: C17.1, C18.1, U3.15 (VCOM)
/VCOM_BUF: C38.1, C39.1, R40.1, R49.2, U6.5 (+), U6.12 (+)
GND: C1.2, C2.1, C3.2, C4.2, C5.2, C6.2, C7.2, C10.2, C11.2, C12.2, C13.2, C14.2, C15.2, C16.2, C17.2, C18.2, C19.2, C26.2, C27.1, C28.2, C29.1, C30.2, C36.1, C37.1, C38.2, C39.2, C42.2, D3.1 (K), J1.3, J1.4, J1.5, J1.6, J1.7, J1.8, J2.S, J2.TN, J3.S, J3.TN, J4.S, J5.S, J6.2, J7.2, J7.4, J7.9, J7.10, R14.2, R15.2, R16.2, R17.2, R41.2, R42.1, R43.1, R48.2, R50.2, R51.2, RV1.1, RV2.1, SW1.2, SW2.2, SW3.2, U1.1 (GND), U2.1 (GND), U3.2 (XTI), U3.8 (DGND), U3.13 (AD0/~CS(I2S/~LJ)), U3.21 (AGND), U6.11 (V-), Y1.2 (GND)
unnamed: C20.2, R24.2, R26.1, R44.1, U6.1
unnamed: C21.2, R25.2, R27.1, R45.1, U6.8
unnamed: C34.2, R34.2, R36.1, R38.1, U5.1
unnamed: C35.2, R35.2, R37.1, R39.1, U5.7
unnamed: D3.2 (A), R53.2
unnamed: R28.1, R46.2, U6.7
unnamed: R29.1, R47.2, U6.14
unnamed: C5.1, R1.2, U2.3 (VI)
unnamed: C15.1, C16.1, U3.22 (FILT+)
unnamed: R10.2, TP1.1, U3.3 (MCLK)
unnamed: R20.2, U4.3 (+)
unnamed: R22.1, U4.1, U4.2 (-)
unnamed: R21.2, U4.5 (+)
unnamed: R23.1, U4.6 (-), U4.7
unnamed: C36.2, R32.2, R42.2, U5.3 (+)
unnamed: C34.1, R30.2, R34.1, U5.2 (-)
unnamed: C37.2, R33.2, R43.2, U5.5 (+)
unnamed: C35.1, R31.2, R35.1, U5.6 (-)
unnamed: C20.1, R22.2, R24.1, U6.2 (-)
unnamed: R44.2, R46.1, U6.6 (-)
unnamed: C21.1, R23.2, R25.1, U6.9 (-)
unnamed: R45.2, R47.1, U6.13 (-)
unnamed: R10.1, Y1.3 (OUT)

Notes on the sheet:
MCU BOARD LINK: J6/J7 1x10 2.54 mm male headers (plastic on the carrier F side); the ESP32-S3 MCU board (32bit-mcu) solders on top. RESET (EN) / BOOT (GPIO0) on the carrier B side: hold BOOT, press RESET = ESP32-S3 ROM download mode on the USB-C (recovery only).
CONTROLS (firmware-defined): RV1 / RV2 50k on the ESP32-S3 ADC1 (0..3.03 V), SW3 MODE to GND, MODE LED D3 through R53 1k. Not in the audio path.
POWER: +12V -> D2 -> +12V_F (op-amps; U1 AMS1117-5.0 -> +5VA; R1 22R -> U2 AMS1117-3.3 -> +3V3 -> FB1 -> +3V3_C); -12V -> D1 -> -12V_F
PWR_FLAG: GND/+12V/-12V at J1; +12V_F/-12V_F behind D2/D1; V3_IN behind R1; +3V3_C behind FB1.
CS4272 CODEC: I2C control port, address 0x10, 100 kHz. Master, external MCLK 24.576 MHz (XTI = GND): 512 / 256 / 128 x Fs = 48 / 96 / 192 kHz (Ratio1:0 = 10); SCLK = 64 x Fs to the ESP32-S3 I2S slave. Firmware: RST high, write 03h to 07h (CPEN + PDN) within 10 ms, set the registers, clear PDN. SCLK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
I2S series termination (at the codec) and pull-downs
REFERENCE (+5VA): R49 over R40 + R41 = 0.482 x VA = 2.41 V -> VCOM_BUF (unity inverters, C38 / C39) and VB_IN = VCOM_BUF x 2/2.51 (input drivers, no capacitor). It only sets the ADC common mode; the codec VCOM pin is not loaded. No buffer op-amp (S5).
INPUTS: jack (TN = GND, R50/R51 100k to GND) -> 1k -> U4A/B NE5532 follower (+/-12 V) -> U6 inverting driver on +5VA (-0.255, + at VB_IN) = AIN-; U6 unity inverter about VCOM_BUF = AIN+; 100R per leg, 2.2n C0G across the pair. +/-5.54 V = 5.65 Vpp differential ADC full scale.
BIG MODULAR 32BIT - carrier (jack board), S4: modules/usb-audio S5 audio path + ESP32-S3 MCU board. 2 in / 2 out, DC-coupled +/-5 V, CS4272. Circuit intent: docs/research.md; placement: docs/geometry.json
OUTPUTS: AOUT+/- -> U5A/B difference amplifier (6.8k / 15k, 100p: x2.2, 106 kHz) -> 2k || 2k (1k / 0.5W) -> jack. 4.8 Vpp differential DAC full scale -> +/-5.29 V. The codec common mode (VCOM) cancels: 0 V out at mid-scale and while the codec is in reset.
